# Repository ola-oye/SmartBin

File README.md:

# SmartBin - Automated Organic Waste Processor 
## Overview

SmartBin is an automated system that converts organic waste into compost through a controlled drying and grinding process. The system features odor control using carbon filtration, automated waste level detection, and a custom-designed ESP32-based motherboard for complete process automation.

**Key Features:**
- Automated waste level monitoring using ultrasonic sensors
- Odor control system with carbon filter and exhaust fan
- Controlled drying via 50W heating element
- Automated grinding using 120W AC blender motor with PWM speed control
- Custom PCB design with high/low-voltage isolation
- FreeRTOS-based task management

---

## System Architecture

*System Schematic*

### Process Flow:
1. **Waste Collection** → Ultrasonic sensor monitors fill level
2. **Odor Filtration** → Fan pulls air through carbon filter before exhaust
3. **Drying Stage** → Heating element activates at threshold level
4. **Grinding Stage** → AC motor pulverizes dried waste
5. **Storage** → Processed compost collected in separate compartment

---

## Hardware Design

### Custom Motherboard (KiCad)

*Top layer of SmartBin control board*

*Bottom layer showing power traces and isolation*

**Board Specifications:**
- **Controller:** ESP32-WROOM-32
- **Power Input:** 220V AC mains
- **AC Loads:** 120W blender motor, 50W heating element
- **DC Loads:** 5V fan, 3.3V control logic
- **Protection:** Fuse, optoisolators, flyback diodes
- **PCB Layers:** 2-layer, FR4
- **Dimensions:** [Add dimensions in mm]

### Key Components:

| Component | Purpose | Interface |
|-----------|---------|-----------|
| ESP32 | Main controller | - |
| HC-SR04 | Waste level detection | GPIO |
| TRIAC + Optocoupler | AC motor speed control | PWM |
| Solid State Relay | Heating element control | GPIO |
| 12V/5V Regulators | DC power supply | - |
| Current Sensor | Motor load monitoring | ADC |

### Power Distribution:
```
220V AC ─┬─► AC Motor (via TRIAC dimmer)
         ├─► 50W Heater (via SSR)
         └─► AC-DC Converter ──► 12V ──► 5V ──► 3.3V ESP32
                                      ├─► Fan
                                      └─► Sensors
```
---

### Hardware Setup:

1. **Fabricate PCB:** Upload Gerber files to JLCPCB
2. **Solder Components:** Follow assembly drawing
3. **Connect Sensors:** Wire ultrasonic sensor to designated headers
4. **Power Connections:** 220V AC input via terminal block
5. **Motor Connection:** AC motor to TRIAC output
6. **Heater Connection:** Heating element to SSR output

## Testing & Validation

| Test | Method | Result |
|------|--------|--------|
| Motor speed control | Oscilloscope (PWM waveform) | ±5% accuracy |
| Temperature regulation | Thermocouple logging | ±2°C |
| Level detection | Manual measurement vs sensor | ±2mm |
| Power consumption | AC power meter | 125W max |
| Cycle time | Full dry → grind cycle | 45-60 min |

---

## Challenges & Solutions

| Challenge | Solution |
|-----------|----------|
| AC motor EMI interfering with ESP32 | Added optoisolation, separate ground planes |
| Heating element overshoot | Implemented PID control instead of bang-bang |
| Moisture damage to electronics | Enclosed PCB in sealed compartment |
| Inrush current on motor start | Added soft-start PWM ramp |

---
## Future Improvements

- [ ] WiFi connectivity for remote monitoring
- [ ] Mobile app integration for status alerts
- [ ] Solar power compatibility
- [ ] Automatic compost quality sensing
- [ ] Multiple bin capacity expansion
- [ ] Machine learning for optimal cycle prediction

## Author

**Fatai Oyetunji**  
Computer Science, University of Lagos  
[GitHub](https://github.com/ola-oye) | [LinkedIn](https://linkedin.com/in/olasunkanmi)

---

## Acknowledgments

- University of Lagos Computer Science Department
- NitHub, University of Lagos
- Project supervisor and team members
- Open-source KiCad and ESP32 communities

---

**⭐ If you found this project useful, consider giving it a star!**

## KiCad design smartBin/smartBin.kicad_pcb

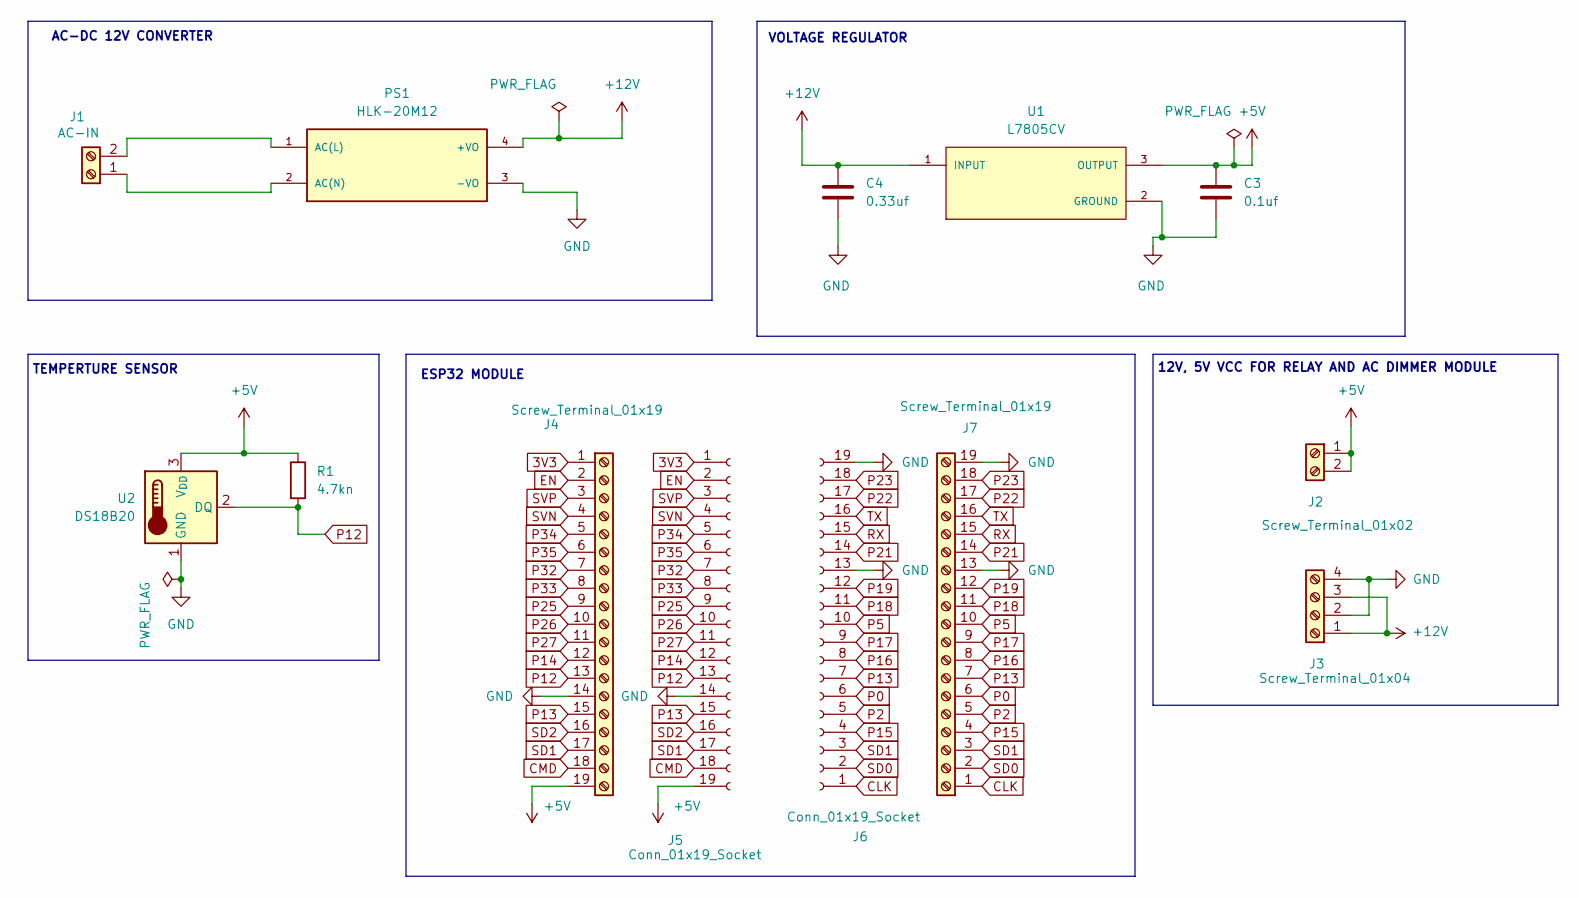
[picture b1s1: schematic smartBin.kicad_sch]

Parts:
C3: 0.1uf; C_0402_1005Metric_Pad0.74x0.62mm_HandSolder
C4: 0.33uf; C_0402_1005Metric_Pad0.74x0.62mm_HandSolder
J1: AC-IN; TerminalBlock_MaiXu_MX126-5.0-02P_1x02_P5.00mm
J2: Screw_Terminal_01x02; TerminalBlock_MaiXu_MX126-5.0-02P_1x02_P5.00mm
J3: Screw_Terminal_01x04; TerminalBlock_MaiXu_MX126-5.0-04P_1x04_P5.00mm
J4, J7: Screw_Terminal_01x19; TerminalBlock_MaiXu_MX126-5.0-19P_1x19_P5.00mm
J5, J6: Conn_01x19_Socket; PinSocket_1x19_P2.54mm_Vertical
PS1: HLK-20M12; CONV_HLK-20M12; PARTREV V1.3
R1: 4.7kn; R_0402_1005Metric_Pad0.72x0.64mm_HandSolder
U1: L7805CV; TO255P1040X460X1968-3; PARTREV 36
U2: DS18B20; TO-92_Inline

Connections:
3V3: J4.1, J5.1
+5V: C3.1, J2.1, J2.2, J4.19, J5.19, R1.1, U1.3 (OUTPUT), U2.3 (V_{DD})
+12V: C4.1, J3.1, J3.3, PS1.4 (+VO), U1.1 (INPUT)
CLK: J6.1, J7.1
CMD: J4.18, J5.18
EN: J4.2, J5.2
GND: C3.2, C4.2, J3.2, J3.4, J4.14, J5.14, J6.13, J6.19, J7.13, J7.19, PS1.3 (-VO), U1.2 (GROUND), U2.1 (GND)
unnamed: J1.1, PS1.2 (AC(N))
unnamed: J1.2, PS1.1 (AC(L))
P0: J6.6, J7.6
P2: J6.5, J7.5
P5: J6.10, J7.10
P12: J4.13, J5.13, R1.2, U2.2 (DQ)
P13: J4.15, J5.15, J6.7, J7.7
P14: J4.12, J5.12
P15: J6.4, J7.4
P16: J6.8, J7.8
P17: J6.9, J7.9
P18: J6.11, J7.11
P19: J6.12, J7.12
P21: J6.14, J7.14
P22: J6.17, J7.17
P23: J6.18, J7.18
P25: J4.9, J5.9
P26: J4.10, J5.10
P27: J4.11, J5.11
P32: J4.7, J5.7
P33: J4.8, J5.8
P34: J4.5, J5.5
P35: J4.6, J5.6
RX: J6.15, J7.15
SD0: J6.2, J7.2
SD1: J4.17, J5.17, J6.3, J7.3
SD2: J4.16, J5.16
SVN: J4.4, J5.4
SVP: J4.3, J5.3
TX: J6.16, J7.16

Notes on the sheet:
AC-DC 12V CONVERTER
12V, 5V VCC FOR RELAY AND AC DIMMER MODULE
ESP32 MODULE
TEMPERTURE SENSOR
VOLTAGE REGULATOR

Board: 2 copper layers, 13 parts (0 on the bottom side), 37 nets, no tracks yet.

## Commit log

2026-02-13 pcb design
